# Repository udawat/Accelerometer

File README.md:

Accelerometer
=============

A simple Breakout Board for the ADXL345 3-Axis Accelerometer

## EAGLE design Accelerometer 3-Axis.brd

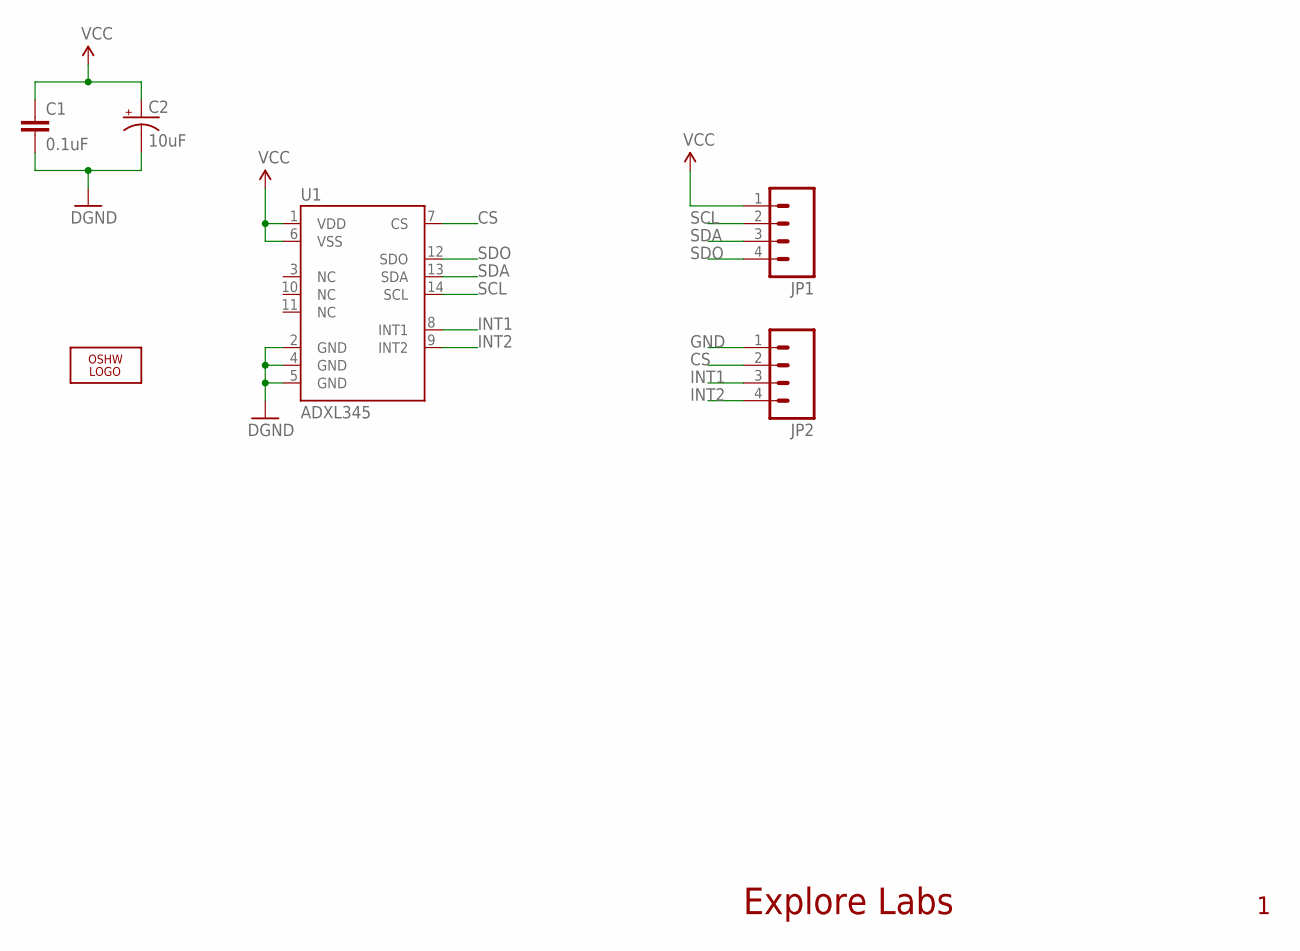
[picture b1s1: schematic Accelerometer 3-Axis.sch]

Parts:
C1: 0.1uF; 0402-CAP
C2: 10uF; EIA3216
JP1, JP2: M04PTH; 1X04
LOGO2: OSHW_LOGO_FILLX0100-NT; OSHW_FILLX100_NOTEXT
U1: ADXL345; LGA14

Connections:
CS: JP2.2, U1.7 (CS)
GND: C1.2, C2.C (-), JP2.1, U1.2 (GND), U1.4 (GND), U1.5 (GND)
INT1: JP2.3, U1.8 (INT1)
INT2: JP2.4, U1.9 (INT2)
SCL: JP1.2, U1.14 (SCL)
SDA: JP1.3, U1.13 (SDA)
SDO: JP1.4, U1.12 (SDO)
VCC: C1.1, C2.A (+), JP1.1, U1.1 (VDD), U1.6 (VSS)

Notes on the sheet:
Explore Labs

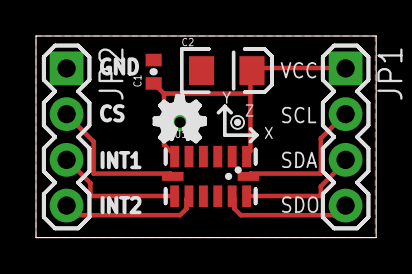
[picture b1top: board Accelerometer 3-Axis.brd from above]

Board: 2 copper layers, 18.9 x 11.2 mm, 6 parts (0 on the bottom side), 8 nets.

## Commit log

2012-11-22 Gerber Data for Board Fabrication added

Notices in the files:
parts and their libraries:
SparkFun-Sensors: Licensing: CC v3.0 Share-Alike You are welcome to use this library for commercial purposes.
SparkFun-Aesthetics: Released under the Creative Commons
SparkFun-Aesthetics: http://creativecommons.org/licenses/by-sa/3.0
